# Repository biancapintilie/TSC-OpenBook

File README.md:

# OpenBook

## Descriere
OpenBook este un dispozitiv portabil bazat pe microcontrollerul ESP32-C6, proiectat pas cu pas, incepand cu schema componentelor, apoi schema electrica si in final modelul 3D al acestuia, urmarind schemele si indrumarile oferite in enuntul temei.
Pentru schematic am descarcat libraria din enunt si am folosit piesele de acolo pentru a realiza componentele si le-am asezat in frame exact ca in exemplul din enunt.
La partea de PCB am amplasat piesele dupa desenul dat, urmand masuratorile exacte, iar rutarea am facut-o folosind combinatia intre autorute si rute manuale pentru evitarea erorilor, fiind nevoita sa mai misc piesele incat sa pot ruta cat mai ok. Apoi am facut planurile de masa, atat pentru top cat si pentru bottom.
In final, am cautat modelul 3D pentru fiecare piesa pentru a-l adauga la forma 3D finala a dispozitivului, impreuna cu carcasa acestuia.

## Hardware

### **1. Microcontroller U2 – ESP32-C6-WROOM-1-N8**
#### - Modul principal de procesare, cu:
 - Procesor RISC-V single-core, 160 MHz
 - 	Wi-Fi 6 și Bluetooth 5.0
 - 	8 MB flash
 - 	Alimentare: 3.3V
#### - Conexiuni principale:
- SPI (pentru e-paper și microSD)
- I2C (pentru RTC și senzori)
- GPIO (pentru butoane, LED-uri, control power)

#### - Pini folosiți ESP32-C6:
| Semnal | Pin ESP32	| Funcție |
|--------|------------|---------|
| MOSI | GPIO10 |	Date spre e-paper |
| SCK | GPIO9 |	Ceas SPI |
| CS | GPIO8 | Chip Select |
| DC | GPIO7 | Data/Command |
| RST | GPIO5 |	Reset display |
| BUSY | GPIO6 | Status afișaj |

### 2. Afișaj e-paper J1 – FH34SRJ-24S-0.5SH
- Afișaj conectat prin SPI
- Condensatori de filtrare în jurul e-paper:
- EPD_C1–C12: 0.1–1uF (filtrare alimentare și stabilizare semnal)
- MOSFET: Q3 – SI1308EDL (pentru comutarea alimentării e-paperului)

### 3. Memorie și stocare U1 – W25Q512JVEIQ
- 64MB NOR Flash SPI
- Pentru stocarea fișierelor locale, fonturi, etc.
microSD (SPI shared):
- Partajat cu SPI-ul e-paper
- CS separat (ex: GPIO15)

### 4. Alimentare & management baterie Li-Po 3.7V
#### - Încărcare:
- MCP73831 (U MCP73831) – încărcare baterie prin USB
- Diodă protecție: D3–D5 (MBR0530)
#### - Monitorizare baterie:
- MAX17048 (U4) – Fuel Gauge via I2C
- Divizor rezistiv: R1_BAT, R2_BAT
- ADC ESP32: GPIO1
#### - Condensatori alimentare:
- C1_BAT, C2_BAT, C3, etc. – diverse capacități pentru filtrare și stabilizare (4.7uF – 100uF)

### 5. Ceas în timp real (RTC) U3 – DS3231SN
- RTC cu I2C, extrem de precis
- Backup pe supercapacitor (C10_SUPERCAP)
- Conexiune I2C: GPIO21 (SDA), GPIO22 (SCL)

### 6. Senzor SENSOR2 – BME680
- Senzor de mediu: temperatură, presiune, umiditate, COV
- Interfață I2C (partajat cu RTC)

### 7. Interfață utilizator
#### - Butoane fizice:
- BOOT_BUTTON, RESET_BUTTON, CHANGE_BUTTON
- Conectate pe GPIO2, GPIO3, GPIO4 (cu pull-up R_RESET, R_CHANGE etc.)
#### - LED RGB pentru feedback:
- CHG_LED – conectat la GPIO18 (PWM)

### 8. Protecție și filtrare
- D1 – USBLC6-2SC6Y – protecție ESD pe linia USB
- PGB1010603MR (D6, D8–D12) – protecție la supratensiune
- PFMF.050.1 – Varistor pentru liniile de alimentare

### 9. Alte circuite pasive
- Filtru LC pe alimentare display: L1 – 68uH, C7, C8
- Diverse rezistențe pull-up/down, limitare curent, etc.:
- R1–R10, R_BOOT, R_PWRUSB, R_CAPACITOR etc.
- Majoritatea în format 0402

### 10. Test Points & Debug
- TP1–TP17: puncte de test pentru semnale critice
- UART debug: GPIO43 (TX), GPIO44 (RX) – pentru încărcare firmware și debug

### Carcasă și design fizic
- PCB în format compact, optimizat pentru portabilitate
- Carcasă printată 3D
- Acces facil la conectorul USB-C (J2) pentru încărcare

## Schema Bloc

## Bill Of Materials

| Componenta | Link | Datasheet |
|-----------|--------------|-----------|
| Capacitor 0402 | [Model](https://componentsearchengine.com/part-view/CC0402MRX5R5BB106/YAGEO) | [Datasheet](https://componentsearchengine.com/Datasheets/2/CC0402MRX5R5BB106.pdf) |
| CPH3225A | [Model](https://www.snapeda.com/parts/CPH3225A/Seiko+Instruments/view-part/?ref=eda) | [Datasheet](https://www.snapeda.com/parts/CPH3225A/Seiko+Instruments/view-part/?ref=eda) |
| RCL 3528 | [Model](https://www.snapeda.com/parts/TAJB475K025RNJ/AVX/view-part/?ref=dk&t=capacitor%203528&con_ref=None) | [Datasheet](https://s3.amazonaws.com/snapeda/datasheet/TAJB475K025RNJ_AVX.pdf) |
| Resistor 0402 | [Model](https://componentsearchengine.com/part-view/R0402%201%25%20100%20K%20(RC0402FR-07100KL)/YAGEO) | [Datasheet](https://www.yageo.com/upload/media/product/products/datasheet/rchip/PYu-RC_Group_51_RoHS_L_12.pdf) |
| Dioda MBR0530 | [Model](https://eu.mouser.com/ProductDetail/KYOCERA-AVX/SD0805S020S1R0?qs=jCA%252BPfw4LHbpkAoSnwrdjw%3D%3D) | [Datasheet](https://ro.mouser.com/datasheet/2/40/schottky-3165252.pdf) |
| Dioda PGB1010603MR | [Model](https://www.snapeda.com/parts/PGB1010603MR/Littelfuse/view-part/?ref=eda) | [Datasheet](https://www.snapeda.com/parts/PGB1010603MR/Littelfuse%20Inc./datasheet/) |
| Buton | [Model](https://industry.panasonic.com/global/en/products/control/switch/light-touch/number/evqpuj02k) | [Datasheet](https://industry.panasonic.com/global/en/downloads?tab=catalog&small_g_cd=203&part_no=EVQPUJ02K) |
| LED 0603 | [Model](https://www.snapeda.com/parts/KP-1608SURCK/Kingbright/view-part/?ref=search&t=LED%200603) | [Datasheet](https://www.snapeda.com/parts/KP-1608SURCK/Kingbright/datasheet/) |
| Sensor BME680 | [Model](https://www.digikey.ro/en/models/7401317) | [Datasheet](https://www.bosch-sensortec.com/media/boschsensortec/downloads/datasheets/bst-bme680-ds001.pdf) |
| SJ | [Model](https://grabcad.com/library/solder-jumpers-1) | [Datasheet](https://grabcad.com/library/solder-jumpers-1) |
| ESP32C6 | [Model](https://ro.mouser.com/ProductDetail/EPCOS-TDK/B72520T0350K062?qs=dEfas%2FXlABIszF52uu7vrg%3D%3D) | [Datasheet](https://www.snapeda.com/parts/RC0603JR-070RL/Yageo/datasheet/) |
| FH34SRJ-24S-0.5SH (J1) | [Model](https://www.snapeda.com/parts/FH34SRJ-24S-0.5SH(99)/Hirose/view-part/) | [Datasheet](https://www.snapeda.com/parts/FH34SRJ-24S-0.5SH(99)/Hirose%20Connector/datasheet/) |
| USB4110-GF-A (J2) | [Model](https://componentsearchengine.com/part-view/USB4110-GF-A/GCT%20(GLOBAL%20CONNECTOR%20TECHNOLOGY)) | [Datasheet](https://gct.co/files/drawings/usb4110.pdf) |
| QWIIC Connector (J3) | [Model](https://www.snapeda.com/parts/PRT-14417/SparkFun/view-part/) | [Datasheet](https://www.snapeda.com/parts/PRT-14417/SparkFun%20Electronics/datasheet/) |
| 112A-TAAR-R03 (J4)| [Model](https://www.snapeda.com/parts/112A-TAAR-R03/Attend/view-part/) | [Datasheet](https://www.snapeda.com/parts/112A-TAAR-R03/Attend/datasheet/) |
| 744043680 (L1)| [Model](https://ro.mouser.com/ProductDetail/Wurth-Elektronik/744043680?qs=PGXP4M47uW6VkZq%252BkzjrHA%3D%3D) | [Datasheet](https://www.we-online.com/components/products/datasheet/744043680.pdf) |
| DMG2305UX-7 (Q1, Q2) | [Model](https://componentsearchengine.com/part-view/DMG2305UX-7/Diodes%20Incorporated) | [Datasheet](https://www.snapeda.com/parts/SI1308EDL-T1-GE3/Vishay%20Siliconix/datasheet/) |
| SI1308EDL-T1-GE3 (Q3) | [Model](https://componentsearchengine.com/part-view/SI1308EDL-T1-GE3/Vishay) | [Datasheet](https://www.snapeda.com/parts/SI1308EDL-T1-GE3/Vishay%20Siliconix/datasheet/) |
| W25Q512JVEIQ (U1) | [Model](https://www.snapeda.com/parts/W25Q512JVEIQ/Winbond+Electronics/view-part/?ref=eda) | [Datasheet](https://www.winbond.com/resource-files/W25Q512JV%20SPI%20RevB%2006252019%20KMS.pdf) |
| ESP32C6 WROOM-1-N8 (U2) | [Model](https://www.snapeda.com/parts/ESP32-C6-WROOM-1-N8/Espressif+Systems/view-part/?ref=eda) | [Datasheet](https://www.snapeda.com/parts/ESP32-C6-WROOM-1-N8/Espressif+Systems/view-part/?ref=eda) |
| DS3231SN (U3) | [Model](https://www.snapeda.com/parts/DS3231SN%23/Analog+Devices/view-part/?ref=eda) | [Datasheet](https://www.snapeda.com/parts/DS3231SN%23/Analog%20Devices/datasheet/) |
| MAX17048G+T10 (U4) | [Model](https://www.snapeda.com/parts/MAX17048G+T10/Analog+Devices/view-part/?ref=eda) | [Datasheet](https://www.snapeda.com/parts/MAX17048G+T10/Analog%20Devices/datasheet/) |
| MCP73831 Power Management (U5) | [Model](https://www.snapeda.com/parts/MCP73831T-2ACI/OT/Microchip/view-part/) | [Datasheet](https://www.snapeda.com/parts/MCP73831T-2ACI/OT/Microchip/datasheet/) |
| BD5229G-TR (IC1) | [Model](https://www.digikey.ee/en/models/658502) | [Datasheet](https://fscdn.rohm.com/en/products/databook/datasheet/ic/power/voltage_detector/bd52xxg-e.pdf) |
| XC6220A331MR-G (IC4) | [Model](https://componentsearchengine.com/part-view/XC6220A331MR-G/Torex) | [Datasheet](https://product.torexsemi.com/system/files/series/xc6220.pdf) |

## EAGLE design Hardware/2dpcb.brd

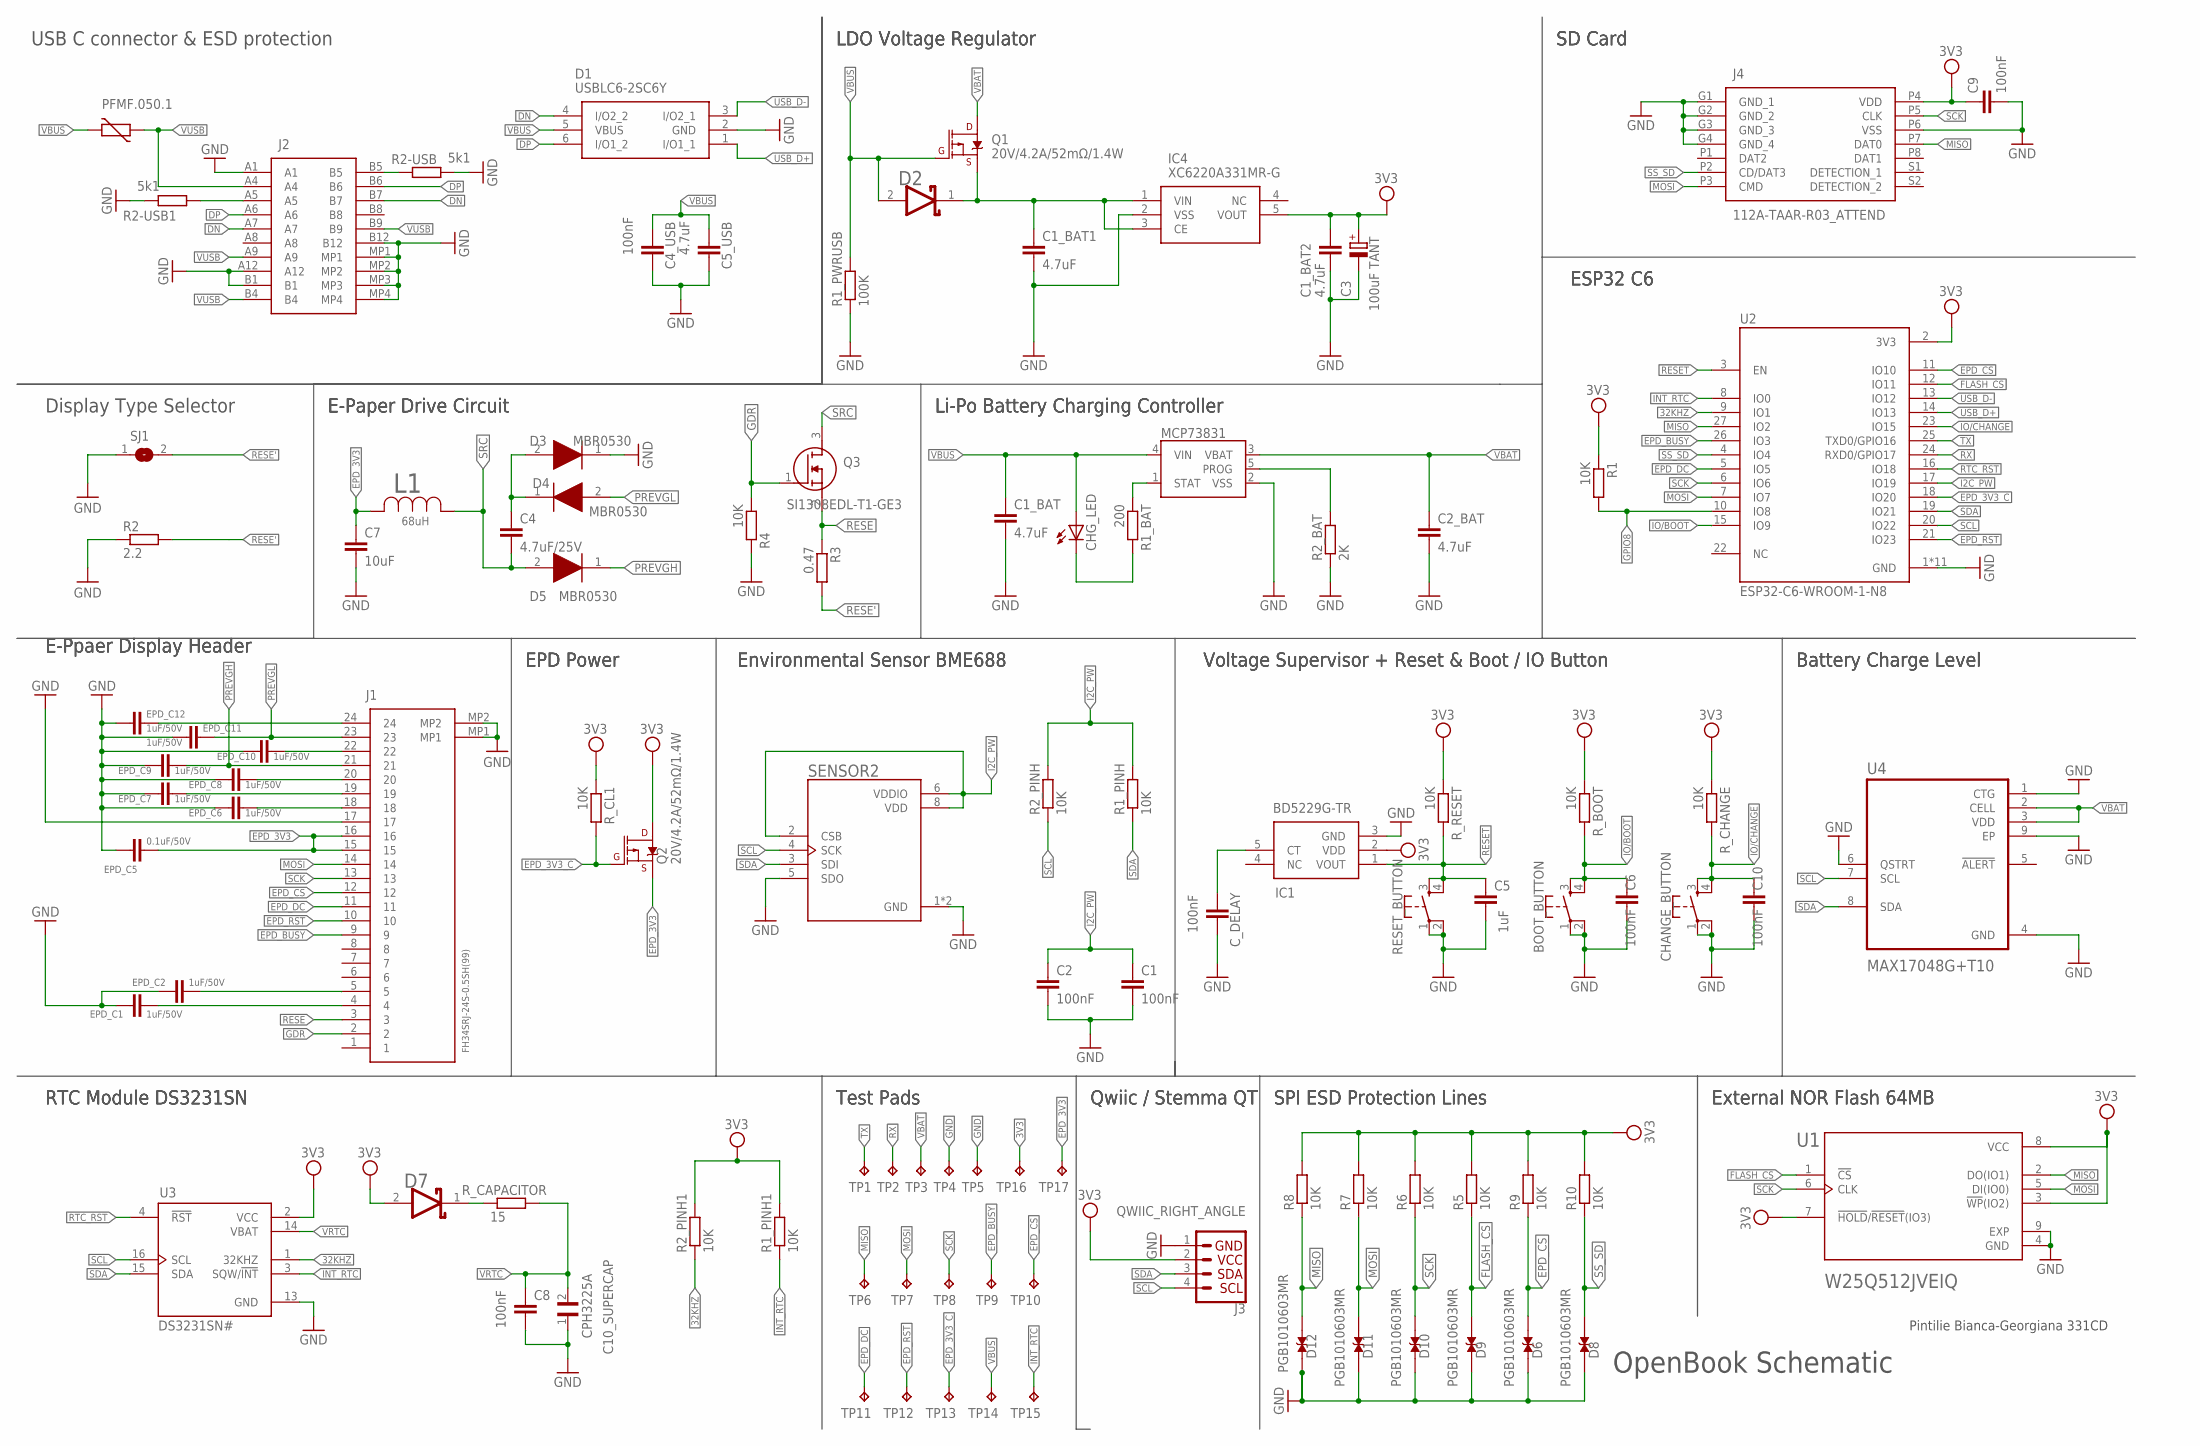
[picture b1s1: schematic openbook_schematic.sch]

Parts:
BOOT_BUTTON: BUTTON_CUSYOMV1; MYBUTTON
C1, C2, C4_USB, C6, C8, C9, C10: 100nF; EAGLE-LTSPICE_C0402
C1_BAT, C1_BAT1, C1_BAT2, C2_BAT, C5_USB: 4.7uF; EAGLE-LTSPICE_C0402
C3: 100uF TANT; RCL_CT3528
C4: 4.7uF/25V; EAGLE-LTSPICE_C0402
C5: 1uF; EAGLE-LTSPICE_C0402
C7: 10uF; EAGLE-LTSPICE_C0402
C10_SUPERCAP: CPH3225A; CAPCP3225X100N
CHANGE_BUTTON: BUTTON_CUSYOMV1; MYBUTTON
CHG_LED: ADAFRUIT_LEDCHIP-LED0603; ADAFRUIT_CHIP-LED0603
C_DELAY: 100nF; EAGLE-LTSPICE_C0402
D1: USBLC6-2SC6Y; SOT95P280X145-6N
D2, D7: ESP32_WROVER_AVX---SD0805S020S1R0_AVX_SD0805S020S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; ESP32_WROVER_AVX---SD0805S020S1R0_AVX_SD0805S020S1R0_0
D3, D4, D5: MBR0530; SOD3716X135N
D6, D8, D9, D10, D11, D12: PGB1010603MR; DIOC1608X36N
EPD_C1, EPD_C2, EPD_C6, EPD_C7, EPD_C8, EPD_C9, EPD_C10, EPD_C11, EPD_C12: 1uF/50V; ESP32_WROVER_EAGLE-LTSPICE_C0402
EPD_C5: 0.1uF/50V; ESP32_WROVER_EAGLE-LTSPICE_C0402
IC1: BD5229G-TR; SOT95P280X125-5N
IC4: XC6220A331MR-G; SOT95P280X120-5N
J1: FH34SRJ-24S-0.5SH_99_; FH34SRJ24S05SH99
J2: SAMACSYS_PARTS_USB4110-GF-A; SAMACSYS_PARTS_USB4110GFA
J3: QWIIC_RIGHT_ANGLE; JST04_1MM_RA
J4: 112A-TAAR-R03_ATTEND; 112ATAARR03ATTEND
L1: 68uH; IND_4828-WE-TPC_WRE
MCP73831: ESP32_WROVER_SPARKFUN-IC-POWER_MCP73831; ESP32_WROVER_SPARKFUN-IC-POWER_SOT23-5
PFMF.050.1: ESP32C6_VARISTORCN1812; ESP32C6_VARISTOR_CT/CN1812
Q1, Q2: 20V/4.2A/52mΩ/1.4W; ESP32_WROVER_SPARKFUN-DISCRETESEMI_SOT23-3
Q3: SI1308EDL-T1-GE3; SOT65P210X110-3N
R1, R1_PINH, R1_PINH1, R2_PINH, R2_PINH1, R4, R5, R6, R7, R8, R9, R10: 10K; ESP32_WROVER_EAGLE-LTSPICE_R0402
R1_BAT: 200; ESP32_WROVER_EAGLE-LTSPICE_R0402
R1_PWRUSB: 100K; ESP32_WROVER_EAGLE-LTSPICE_R0402
R2: 2.2; ESP32_WROVER_EAGLE-LTSPICE_R0402
R2-USB, R2-USB1: 5k1; ESP32_WROVER_EAGLE-LTSPICE_R0402
R2_BAT: 2K; ESP32_WROVER_EAGLE-LTSPICE_R0402
R3: 0.47; ESP32_WROVER_EAGLE-LTSPICE_R0402
RESET_BUTTON: BUTTON_CUSYOMV1; MYBUTTON
R_BOOT: 10K; ESP32_WROVER_EAGLE-LTSPICE_R0402
R_CAPACITOR: 15; ESP32_WROVER_EAGLE-LTSPICE_R0402
R_CHANGE: 10K; ESP32_WROVER_EAGLE-LTSPICE_R0402
R_CL1: 10K; ESP32_WROVER_EAGLE-LTSPICE_R0402
R_RESET: 10K; ESP32_WROVER_EAGLE-LTSPICE_R0402
SENSOR2: ESP32_WROVER_BME680_BME680; ESP32_WROVER_BME680_PSON80P300X300X100-8N
SJ1: SJ
TP1, TP2, TP3, TP4, TP5, TP6, TP7, TP8, TP9, TP10, TP11, TP12, TP13, TP14, TP15, TP16, TP17: TPTP20R; TP20R
U1: W25Q512JVEIQ; SON127P600X800X80-9N
U2: ESP32-C6-WROOM-1-N8; XCVR_ESP32-C6-WROOM-1-N8
U3: DS3231SN#; SOIC127P1032X265-16N
U4: MAX17048G+T10; SON50P200X200X80-9N

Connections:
3V3: C1_BAT2.1, C3.+, C9.1, D7.2 (ANODE), IC1.2 (VDD), IC4.5 (VOUT), J3.2, J4.P4 (VDD), Q2.3 (D), R1.1, R1_PINH1.2, R2_PINH1.2, R5.2, R6.2, R7.2, R8.2, R9.2, R10.2, R_BOOT.1, R_CHANGE.1, R_CL1.1, R_RESET.1, TP16.TP, U1.3 (!WP!(IO2)), U1.7 (!HOLD!/!RESET!(IO3)), U1.8 (VCC), U2.2 (3V3), U3.2 (VCC)
32KHZ: R2_PINH1.1, U2.9 (IO1), U3.1 (32KHZ)
DN: D1.4 (I/O2_2), J2.A7, J2.B7
DP: D1.6 (I/O1_2), J2.A6, J2.B6
EPD_3V3: C7.1, EPD_C5.1, J1.15, J1.16, L1.2, Q2.2 (S), TP17.TP
EPD_3V3_C: Q2.1 (G), R_CL1.2, TP13.TP, U2.18 (IO20)
EPD_BUSY: J1.9, TP9.TP, U2.26 (IO3)
EPD_CS: D6.2, J1.12, R9.1, TP10.TP, U2.11 (IO10)
EPD_DC: J1.11, TP11.TP, U2.5 (IO5)
EPD_RST: J1.10, TP12.TP, U2.21 (IO23)
FLASH_CS: D9.2, R5.1, U1.1 (!CS), U2.12 (IO11)
GDR: J1.2, Q3.1 (G), R4.1
GND: BOOT_BUTTON.1, BOOT_BUTTON.2, C1.2, C1_BAT.2, C1_BAT1.2, C1_BAT2.2, C2.2, C2_BAT.2, C3.-, C4_USB.2, C5.2, C5_USB.2, C6.2, C7.2, C8.2, C9.2, C10.2, C10_SUPERCAP.1, CHANGE_BUTTON.1, CHANGE_BUTTON.2, C_DELAY.2, D1.2 (GND), D3.1 (K), D6.1, D8.1, D9.1, D10.1, D11.1, D12.1, EPD_C1.2, EPD_C2.2, EPD_C5.2, EPD_C6.2, EPD_C7.2, EPD_C8.2, EPD_C9.2, EPD_C10.2, EPD_C11.2, EPD_C12.2, IC1.3 (GND), IC4.2 (VSS), J1.17, J1.MP1, J1.MP2, J2.A1, J2.A12, J2.B1, J2.B12, J2.MP1, J2.MP2, J2.MP3, J2.MP4, J3.1, J4.G1 (GND_1), J4.G2 (GND_2), J4.G3 (GND_3), J4.G4 (GND_4), J4.P6 (VSS), MCP73831.2 (VSS), R1_PWRUSB.1, R2.1, R2-USB.2, R2-USB1.1, R2_BAT.1, R4.2, RESET_BUTTON.1, RESET_BUTTON.2, SENSOR2.1 (GND), SENSOR2.5 (SDO), SENSOR2.7 (GND), SJ1.1, TP4.TP, TP5.TP, U1.4 (GND), U1.9 (EXP), U2.1 (GND), U2.28 (GND), U2.29_1 (GND), U2.29_2 (GND), U2.29_3 (GND), U2.29_4 (GND), U2.29_5 (GND), U2.29_6 (GND), U2.29_7 (GND), U2.29_8 (GND), U2.29_9 (GND), U3.13 (GND), U4.1 (CTG), U4.4 (GND), U4.6 (QSTRT), U4.9 (EP)
GPIO8: R1.2, U2.10 (IO8)
I2C_PW: C1.1, C2.1, R1_PINH.2, R2_PINH.2, SENSOR2.2 (CSB), SENSOR2.6 (VDDIO), SENSOR2.8 (VDD), U2.17 (IO19)
INT_RTC: R1_PINH1.1, TP15.TP, U2.8 (IO0), U3.3 (SQW/!INT)
IO/BOOT: BOOT_BUTTON.3, BOOT_BUTTON.4, C6.1, R_BOOT.2, U2.15 (IO9)
IO/CHANGE: C10.1, CHANGE_BUTTON.3, CHANGE_BUTTON.4, R_CHANGE.2, U2.23 (IO15)
MISO: D12.2, J4.P7 (DAT0), R8.1, TP6.TP, U1.2 (DO(IO1)), U2.27 (IO2)
MOSI: D11.2, J1.14, J4.P3 (CMD), R7.1, TP7.TP, U1.5 (DI(IO0)), U2.7 (IO7)
unnamed: EPD_C10.1, J1.22
unnamed: EPD_C8.1, J1.20
unnamed: EPD_C6.1, J1.18
unnamed: C4.1, D3.2 (A), D4.1 (K)
unnamed: EPD_C7.1, J1.19
unnamed: EPD_C1.1, J1.4
unnamed: EPD_C2.1, J1.5
unnamed: J2.B5, R2-USB.1
unnamed: J2.A5, R2-USB1.2
unnamed: EPD_C12.1, J1.24
unnamed: C1_BAT1.1, D2.1 (CATHODE), IC4.1 (VIN), IC4.3 (CE), Q1.2 (S)
unnamed: MCP73831.1 (STAT), R1_BAT.1
unnamed: CHG_LED.C, R1_BAT.2
unnamed: MCP73831.5 (PROG), R2_BAT.2
unnamed: C_DELAY.1, IC1.5 (CT)
unnamed: D7.1 (CATHODE), R_CAPACITOR.1
PREVGH: D5.1 (K), EPD_C9.1, J1.21
PREVGL: D4.2 (A), EPD_C11.1, J1.23
RESE: J1.3, Q3.2 (S), R3.1
RESE': R2.2, R3.2, SJ1.2
RESET: C5.1, IC1.1 (VOUT), RESET_BUTTON.3, RESET_BUTTON.4, R_RESET.2, U2.3 (EN)
RTC_RST: U2.16 (IO18), U3.4 (!RST)
RX: TP2.TP, U2.24 (RXD0/GPIO17)
SCK: D10.2, J1.13, J4.P5 (CLK), R6.1, TP8.TP, U1.6 (CLK), U2.6 (IO6)
SCL: J3.4, R2_PINH.1, SENSOR2.4 (SCK), U2.20 (IO22), U3.16 (SCL), U4.7 (SCL)
SDA: J3.3, R1_PINH.1, SENSOR2.3 (SDI), U2.19 (IO21), U3.15 (SDA), U4.8 (SDA)
SRC: C4.2, D5.2 (A), L1.1, Q3.3 (D)
SS_SD: D8.2, J4.P2 (CD/DAT3), R10.1, U2.4 (IO4)
TX: TP1.TP, U2.25 (TXD0/GPIO16)
USB_D+: D1.1 (I/O1_1), U2.14 (IO13)
USB_D-: D1.3 (I/O2_1), U2.13 (IO12)
VBAT: C2_BAT.1, MCP73831.3 (VBAT), Q1.3 (D), TP3.TP, U4.2 (CELL), U4.3 (VDD)
VBUS: C1_BAT.1, C4_USB.1, C5_USB.1, CHG_LED.A, D1.5 (VBUS), D2.2 (ANODE), MCP73831.4 (VIN), PFMF.050.1.2, Q1.1 (G), R1_PWRUSB.2, TP14.TP
VRTC: C8.1, C10_SUPERCAP.2, R_CAPACITOR.2, U3.14 (VBAT)
VUSB: J2.A4, J2.A9, J2.B4, J2.B9, PFMF.050.1.1

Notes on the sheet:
USB C connector & ESD protection
Display Type Selector
E-Paper Drive Circuit
LDO Voltage Regulator
SD Card
ESP32 C6
Li-Po Battery Charging Controller
E-Ppaer Display Header
EPD Power
Environmental Sensor BME688
Voltage Supervisor + Reset & Boot / IO Button
Battery Charge Level
External NOR Flash 64MB
SPI ESD Protection Lines
Test Pads
Qwiic / Stemma QT
RTC Module DS3231SN
OpenBook Schematic
Pintilie Bianca-Georgiana 331CD

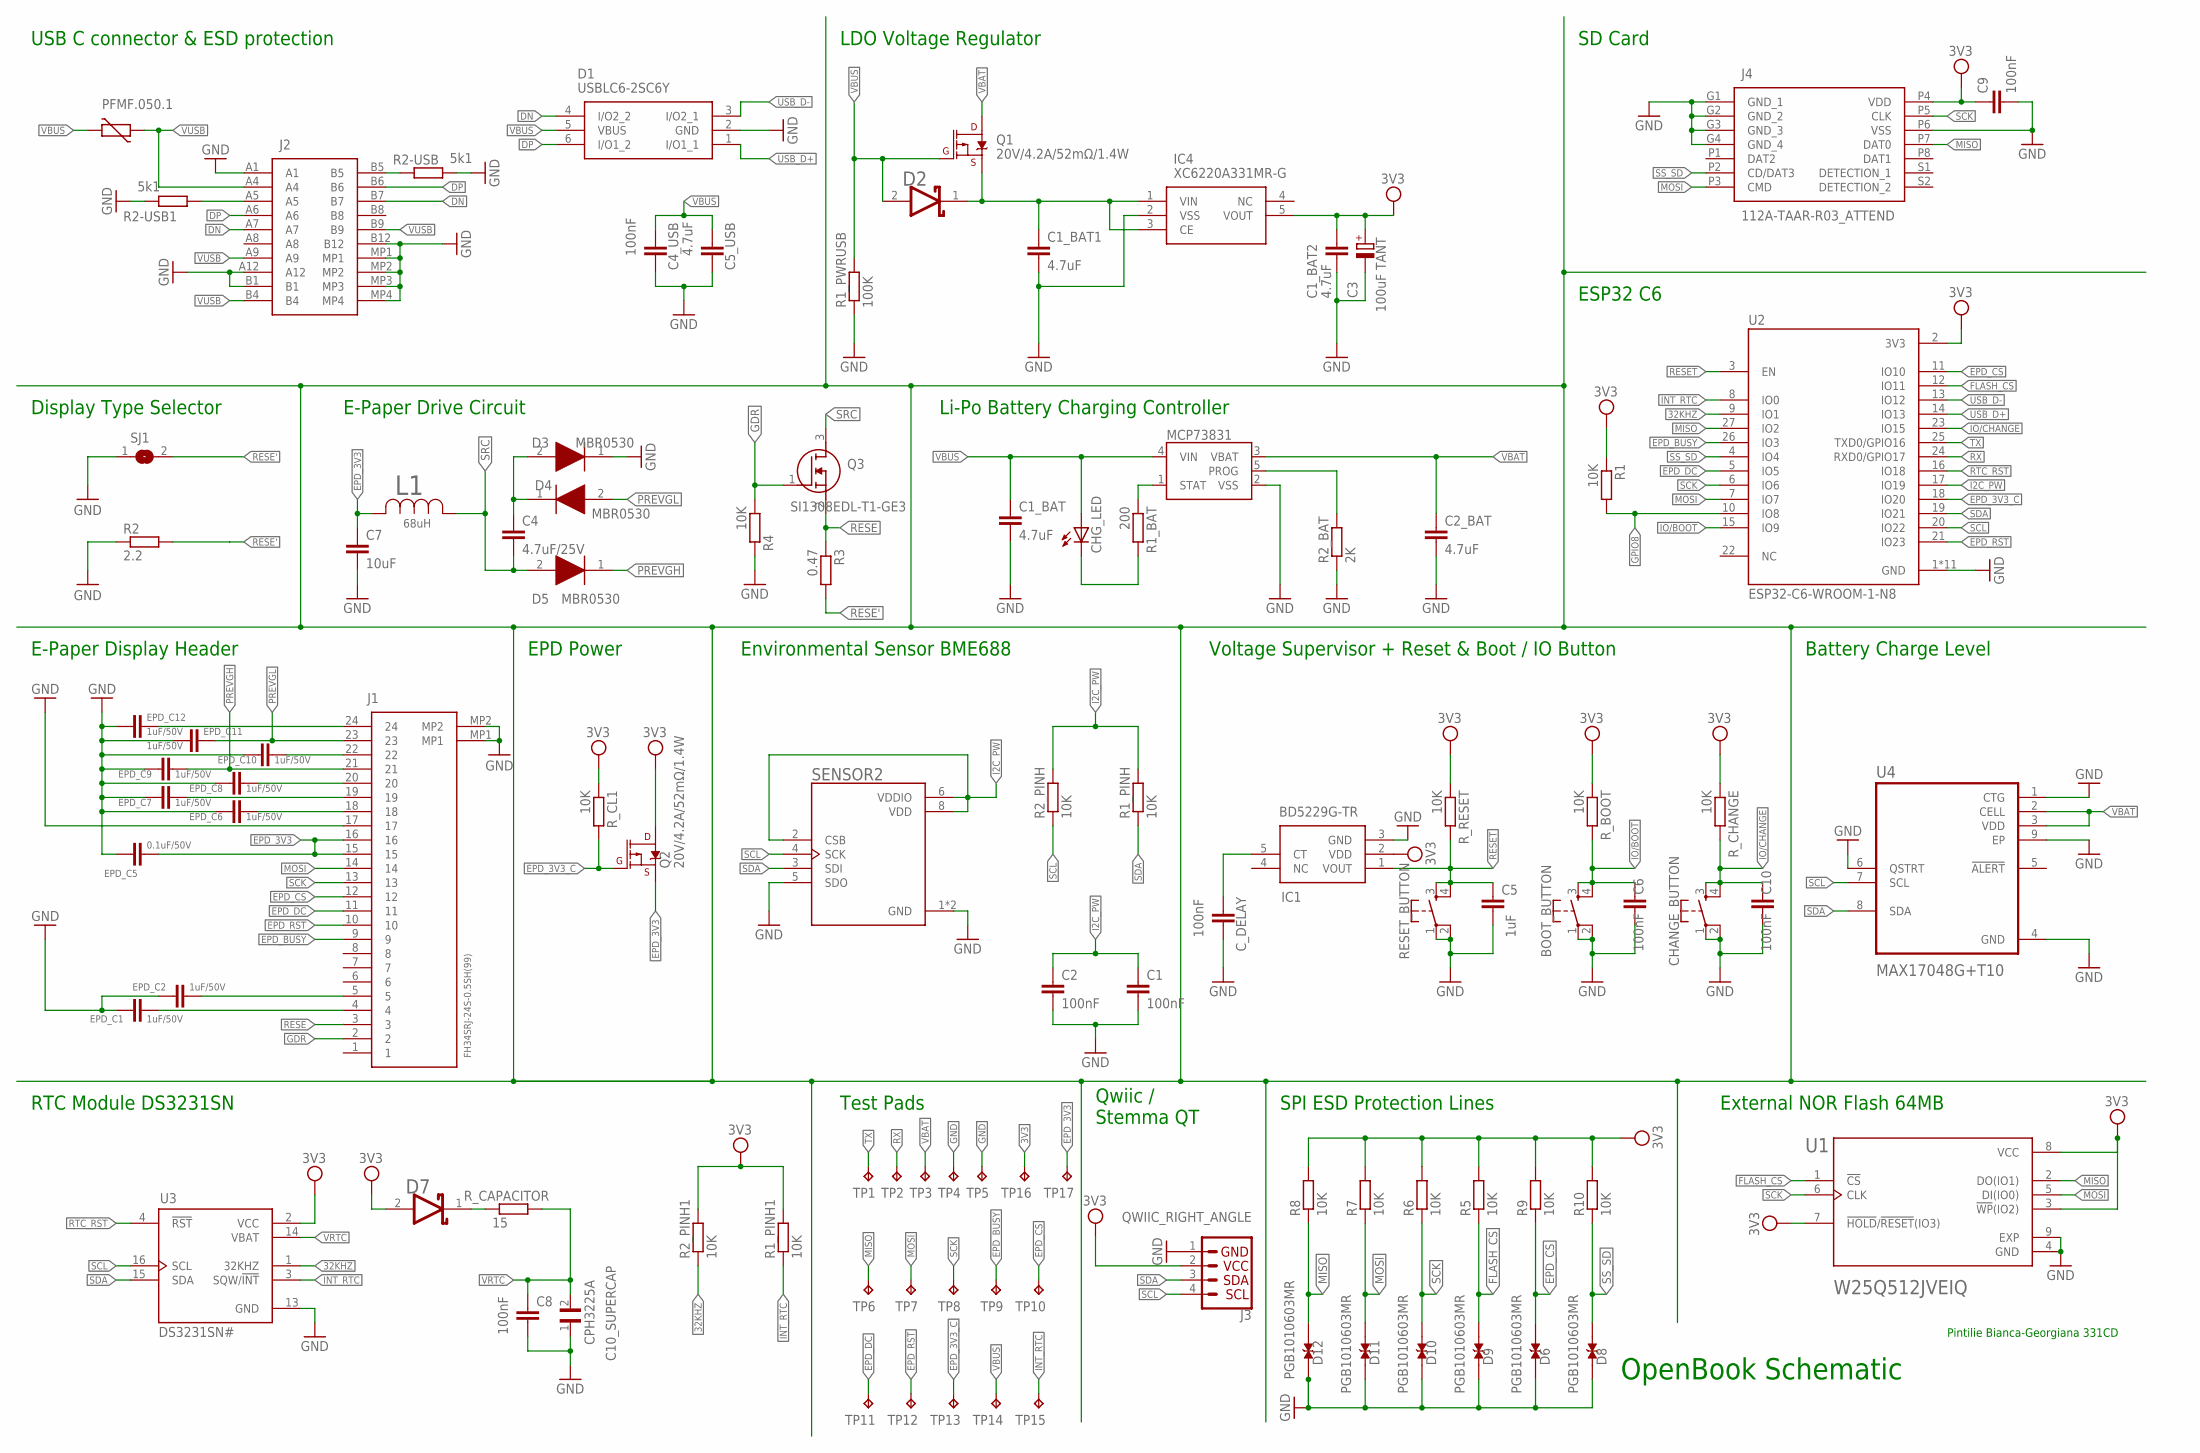
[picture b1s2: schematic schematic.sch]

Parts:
BOOT_BUTTON: BUTTON_CUSYOMV1; MYBUTTON
C1, C2, C4_USB, C6, C8, C9, C10: 100nF; EAGLE-LTSPICE_C0402
C1_BAT, C1_BAT1, C1_BAT2, C2_BAT, C5_USB: 4.7uF; EAGLE-LTSPICE_C0402
C3: 100uF TANT; RCL_CT3528
C4: 4.7uF/25V; EAGLE-LTSPICE_C0402
C5: 1uF; EAGLE-LTSPICE_C0402
C7: 10uF; EAGLE-LTSPICE_C0402
C10_SUPERCAP: CPH3225A; CAPCP3225X100N
CHANGE_BUTTON: BUTTON_CUSYOMV1; MYBUTTON
CHG_LED: ADAFRUIT_LEDCHIP-LED0603; ADAFRUIT_CHIP-LED0603
C_DELAY: 100nF; EAGLE-LTSPICE_C0402
D1: USBLC6-2SC6Y; SOT95P280X145-6N
D2, D7: ESP32_WROVER_AVX---SD0805S020S1R0_AVX_SD0805S020S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; ESP32_WROVER_AVX---SD0805S020S1R0_AVX_SD0805S020S1R0_0
D3, D4, D5: MBR0530; SOD3716X135N
D6, D8, D9, D10, D11, D12: PGB1010603MR; DIOC1608X36N
EPD_C1, EPD_C2, EPD_C6, EPD_C7, EPD_C8, EPD_C9, EPD_C10, EPD_C11, EPD_C12: 1uF/50V; ESP32_WROVER_EAGLE-LTSPICE_C0402
EPD_C5: 0.1uF/50V; ESP32_WROVER_EAGLE-LTSPICE_C0402
IC1: BD5229G-TR; SOT95P280X125-5N
IC4: XC6220A331MR-G; SOT95P280X120-5N
J1: FH34SRJ-24S-0.5SH_99_; FH34SRJ24S05SH99
J2: SAMACSYS_PARTS_USB4110-GF-A; SAMACSYS_PARTS_USB4110GFA
J3: QWIIC_RIGHT_ANGLE; JST04_1MM_RA
J4: 112A-TAAR-R03_ATTEND; 112ATAARR03ATTEND
L1: 68uH; IND_4828-WE-TPC_WRE
MCP73831: ESP32_WROVER_SPARKFUN-IC-POWER_MCP73831; ESP32_WROVER_SPARKFUN-IC-POWER_SOT23-5
PFMF.050.1: ESP32C6_VARISTORCN1812; ESP32C6_VARISTOR_CT/CN1812
Q1, Q2: 20V/4.2A/52mΩ/1.4W; ESP32_WROVER_SPARKFUN-DISCRETESEMI_SOT23-3
Q3: SI1308EDL-T1-GE3; SOT65P210X110-3N
R1, R1_PINH, R1_PINH1, R2_PINH, R2_PINH1, R4, R5, R6, R7, R8, R9, R10: 10K; ESP32_WROVER_EAGLE-LTSPICE_R0402
R1_BAT: 200; ESP32_WROVER_EAGLE-LTSPICE_R0402
R1_PWRUSB: 100K; ESP32_WROVER_EAGLE-LTSPICE_R0402
R2: 2.2; ESP32_WROVER_EAGLE-LTSPICE_R0402
R2-USB, R2-USB1: 5k1; ESP32_WROVER_EAGLE-LTSPICE_R0402
R2_BAT: 2K; ESP32_WROVER_EAGLE-LTSPICE_R0402
R3: 0.47; ESP32_WROVER_EAGLE-LTSPICE_R0402
RESET_BUTTON: BUTTON_CUSYOMV1; MYBUTTON
R_BOOT: 10K; ESP32_WROVER_EAGLE-LTSPICE_R0402
R_CAPACITOR: 15; ESP32_WROVER_EAGLE-LTSPICE_R0402
R_CHANGE: 10K; ESP32_WROVER_EAGLE-LTSPICE_R0402
R_CL1: 10K; ESP32_WROVER_EAGLE-LTSPICE_R0402
R_RESET: 10K; ESP32_WROVER_EAGLE-LTSPICE_R0402
SENSOR2: ESP32_WROVER_BME680_BME680; ESP32_WROVER_BME680_PSON80P300X300X100-8N
SJ1: SJ
TP1, TP2, TP3, TP4, TP5, TP6, TP7, TP8, TP9, TP10, TP11, TP12, TP13, TP14, TP15, TP16, TP17: TPTP20R; TP20R
U1: W25Q512JVEIQ; SON127P600X800X80-9N
U2: ESP32-C6-WROOM-1-N8; XCVR_ESP32-C6-WROOM-1-N8
U3: DS3231SN#; SOIC127P1032X265-16N
U4: MAX17048G+T10; SON50P200X200X80-9N

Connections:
3V3: C1_BAT2.1, C3.+, C9.1, D7.2 (ANODE), IC1.2 (VDD), IC4.5 (VOUT), J3.2, J4.P4 (VDD), Q2.3 (D), R1.1, R1_PINH1.2, R2_PINH1.2, R5.2, R6.2, R7.2, R8.2, R9.2, R10.2, R_BOOT.1, R_CHANGE.1, R_CL1.1, R_RESET.1, TP16.TP, U1.3 (!WP!(IO2)), U1.7 (!HOLD!/!RESET!(IO3)), U1.8 (VCC), U2.2 (3V3), U3.2 (VCC)
32KHZ: R2_PINH1.1, U2.9 (IO1), U3.1 (32KHZ)
DN: D1.4 (I/O2_2), J2.A7, J2.B7
DP: D1.6 (I/O1_2), J2.A6, J2.B6
EPD_3V3: C7.1, EPD_C5.1, J1.15, J1.16, L1.2, Q2.2 (S), TP17.TP
EPD_3V3_C: Q2.1 (G), R_CL1.2, TP13.TP, U2.18 (IO20)
EPD_BUSY: J1.9, TP9.TP, U2.26 (IO3)
EPD_CS: D6.2, J1.12, R9.1, TP10.TP, U2.11 (IO10)
EPD_DC: J1.11, TP11.TP, U2.5 (IO5)
EPD_RST: J1.10, TP12.TP, U2.21 (IO23)
FLASH_CS: D9.2, R5.1, U1.1 (!CS), U2.12 (IO11)
GDR: J1.2, Q3.1 (G), R4.1
GND: BOOT_BUTTON.1, BOOT_BUTTON.2, C1.2, C1_BAT.2, C1_BAT1.2, C1_BAT2.2, C2.2, C2_BAT.2, C3.-, C4_USB.2, C5.2, C5_USB.2, C6.2, C7.2, C8.2, C9.2, C10.2, C10_SUPERCAP.1, CHANGE_BUTTON.1, CHANGE_BUTTON.2, C_DELAY.2, D1.2 (GND), D3.1 (K), D6.1, D8.1, D9.1, D10.1, D11.1, D12.1, EPD_C1.2, EPD_C2.2, EPD_C5.2, EPD_C6.2, EPD_C7.2, EPD_C8.2, EPD_C9.2, EPD_C10.2, EPD_C11.2, EPD_C12.2, IC1.3 (GND), IC4.2 (VSS), J1.17, J1.MP1, J1.MP2, J2.A1, J2.A12, J2.B1, J2.B12, J2.MP1, J2.MP2, J2.MP3, J2.MP4, J3.1, J4.G1 (GND_1), J4.G2 (GND_2), J4.G3 (GND_3), J4.G4 (GND_4), J4.P6 (VSS), MCP73831.2 (VSS), R1_PWRUSB.1, R2.1, R2-USB.2, R2-USB1.1, R2_BAT.1, R4.2, RESET_BUTTON.1, RESET_BUTTON.2, SENSOR2.1 (GND), SENSOR2.5 (SDO), SENSOR2.7 (GND), SJ1.1, TP4.TP, TP5.TP, U1.4 (GND), U1.9 (EXP), U2.1 (GND), U2.28 (GND), U2.29_1 (GND), U2.29_2 (GND), U2.29_3 (GND), U2.29_4 (GND), U2.29_5 (GND), U2.29_6 (GND), U2.29_7 (GND), U2.29_8 (GND), U2.29_9 (GND), U3.13 (GND), U4.1 (CTG), U4.4 (GND), U4.6 (QSTRT), U4.9 (EP)
GPIO8: R1.2, U2.10 (IO8)
I2C_PW: C1.1, C2.1, R1_PINH.2, R2_PINH.2, SENSOR2.2 (CSB), SENSOR2.6 (VDDIO), SENSOR2.8 (VDD), U2.17 (IO19)
INT_RTC: R1_PINH1.1, TP15.TP, U2.8 (IO0), U3.3 (SQW/!INT)
IO/BOOT: BOOT_BUTTON.3, BOOT_BUTTON.4, C6.1, R_BOOT.2, U2.15 (IO9)
IO/CHANGE: C10.1, CHANGE_BUTTON.3, CHANGE_BUTTON.4, R_CHANGE.2, U2.23 (IO15)
MISO: D12.2, J4.P7 (DAT0), R8.1, TP6.TP, U1.2 (DO(IO1)), U2.27 (IO2)
MOSI: D11.2, J1.14, J4.P3 (CMD), R7.1, TP7.TP, U1.5 (DI(IO0)), U2.7 (IO7)
unnamed: EPD_C10.1, J1.22
unnamed: EPD_C8.1, J1.20
unnamed: EPD_C6.1, J1.18
unnamed: C4.1, D3.2 (A), D4.1 (K)
unnamed: EPD_C7.1, J1.19
unnamed: EPD_C1.1, J1.4
unnamed: EPD_C2.1, J1.5
unnamed: J2.B5, R2-USB.1
unnamed: J2.A5, R2-USB1.2
unnamed: EPD_C12.1, J1.24
unnamed: C1_BAT1.1, D2.1 (CATHODE), IC4.1 (VIN), IC4.3 (CE), Q1.2 (S)
unnamed: MCP73831.1 (STAT), R1_BAT.1
unnamed: CHG_LED.C, R1_BAT.2
unnamed: MCP73831.5 (PROG), R2_BAT.2
unnamed: C_DELAY.1, IC1.5 (CT)
unnamed: D7.1 (CATHODE), R_CAPACITOR.1
PREVGH: D5.1 (K), EPD_C9.1, J1.21
PREVGL: D4.2 (A), EPD_C11.1, J1.23
RESE: J1.3, Q3.2 (S), R3.1
RESE': R2.2, R3.2, SJ1.2
RESET: C5.1, IC1.1 (VOUT), RESET_BUTTON.3, RESET_BUTTON.4, R_RESET.2, U2.3 (EN)
RTC_RST: U2.16 (IO18), U3.4 (!RST)
RX: TP2.TP, U2.24 (RXD0/GPIO17)
SCK: D10.2, J1.13, J4.P5 (CLK), R6.1, TP8.TP, U1.6 (CLK), U2.6 (IO6)
SCL: J3.4, R2_PINH.1, SENSOR2.4 (SCK), U2.20 (IO22), U3.16 (SCL), U4.7 (SCL)
SDA: J3.3, R1_PINH.1, SENSOR2.3 (SDI), U2.19 (IO21), U3.15 (SDA), U4.8 (SDA)
SRC: C4.2, D5.2 (A), L1.1, Q3.3 (D)
SS_SD: D8.2, J4.P2 (CD/DAT3), R10.1, U2.4 (IO4)
TX: TP1.TP, U2.25 (TXD0/GPIO16)
USB_D+: D1.1 (I/O1_1), U2.14 (IO13)
USB_D-: D1.3 (I/O2_1), U2.13 (IO12)
VBAT: C2_BAT.1, MCP73831.3 (VBAT), Q1.3 (D), TP3.TP, U4.2 (CELL), U4.3 (VDD)
VBUS: C1_BAT.1, C4_USB.1, C5_USB.1, CHG_LED.A, D1.5 (VBUS), D2.2 (ANODE), MCP73831.4 (VIN), PFMF.050.1.2, Q1.1 (G), R1_PWRUSB.2, TP14.TP
VRTC: C8.1, C10_SUPERCAP.2, R_CAPACITOR.2, U3.14 (VBAT)
VUSB: J2.A4, J2.A9, J2.B4, J2.B9, PFMF.050.1.1

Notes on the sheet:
USB C connector & ESD protection
LDO Voltage Regulator
SD Card
ESP32 C6
Battery Charge Level
External NOR Flash 64MB
SPI ESD Protection Lines
Qwiic / Stemma QT
Test Pads
RTC Module DS3231SN
Display Type Selector
E-Paper Display Header
E-Paper Drive Circuit
Li-Po Battery Charging Controller
EPD Power
Environmental Sensor BME688
Voltage Supervisor + Reset & Boot / IO Button
OpenBook Schematic
Pintilie Bianca-Georgiana 331CD

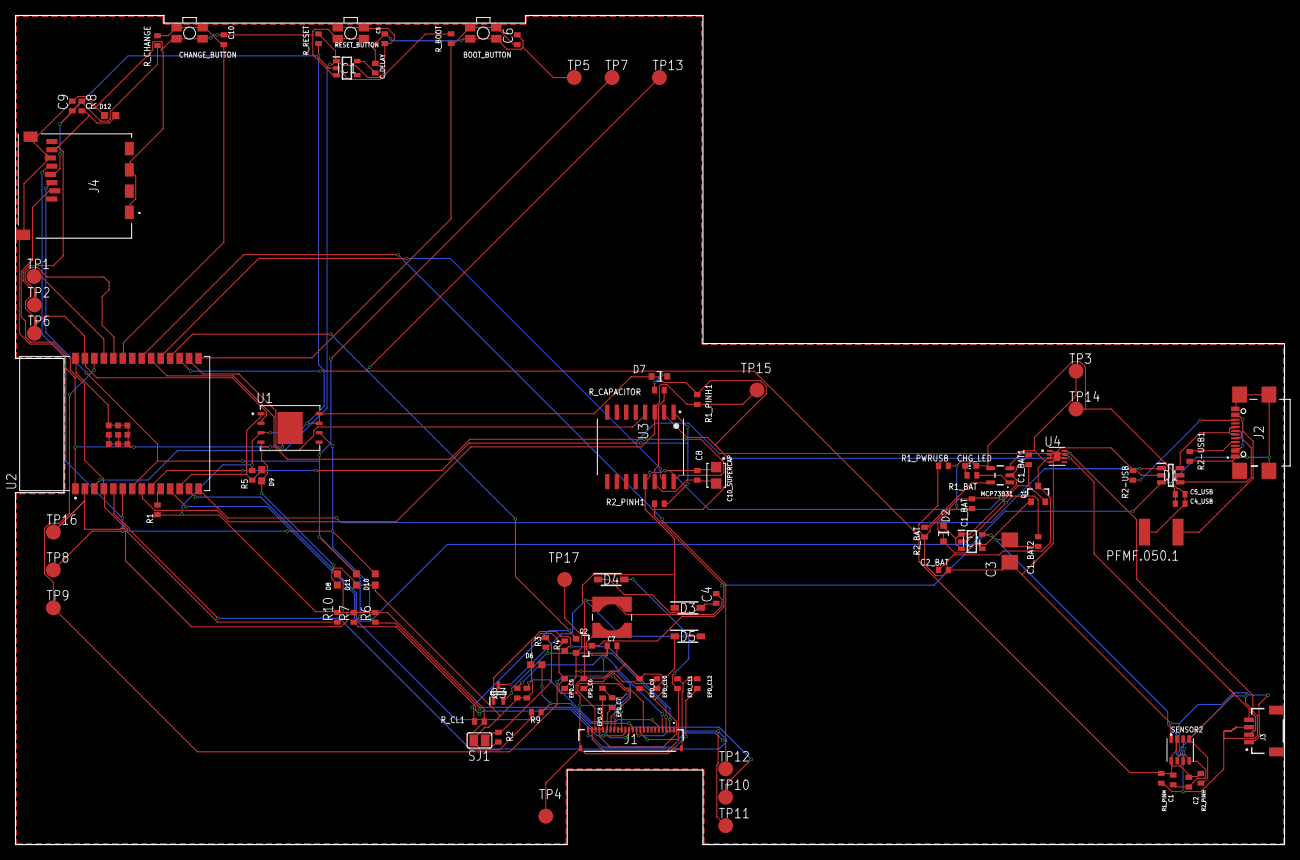
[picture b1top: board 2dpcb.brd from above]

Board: 2 copper layers, 170.2 x 111.2 mm, 103 parts (0 on the bottom side), 55 nets.

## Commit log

2025-04-04 Create LICENSE
2025-04-04 add schematic
2025-04-04 add board
2025-04-06 last changes
2025-04-06 final changes
2025-04-11 fixed schematic issues
2025-04-11 fixed pcb issues
2025-04-11 fixed issues
2025-04-11 fixed all issues

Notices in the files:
parts and their libraries:
COPYRIGHT: Copyright (C) 2024 Ultra Librarian. All rights reserved.
